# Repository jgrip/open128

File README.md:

## Migrated to codeberg <https://codeberg.org/jgrip/Open128>

View this project on [CADLAB.io](https://cadlab.io/project/24751). 

# open128

This is a clone of the Commodore 128 home computer made with KiCad, licensed under [CC BY-SA 4.0](https://creativecommons.org/licenses/by-sa/4.0/).

It contains both schematic and PCB layout, based on the Neo128 project by me.
This PCB has not yet been manufactured and tested however there are minimal changes compared to the well tested Neo128.

Some of the components have been copied from the [bit-preserve project](https://github.com/baldengineer/bit-preserve) and modified.

For Bill of Material and other documentation, please see https://c128.se

-----
This work is licensed under a
[Creative Commons Attribution-ShareAlike 4.0 International License][cc-by-sa].

[![CC BY-SA 4.0][cc-by-sa-image]][cc-by-sa]

[cc-by-sa]: http://creativecommons.org/licenses/by-sa/4.0/
[cc-by-sa-image]: https://licensebuttons.net/l/by-sa/4.0/88x31.png
[cc-by-sa-shield]: https://img.shields.io/badge/License-CC%20BY--SA%204.0-lightgrey.svg

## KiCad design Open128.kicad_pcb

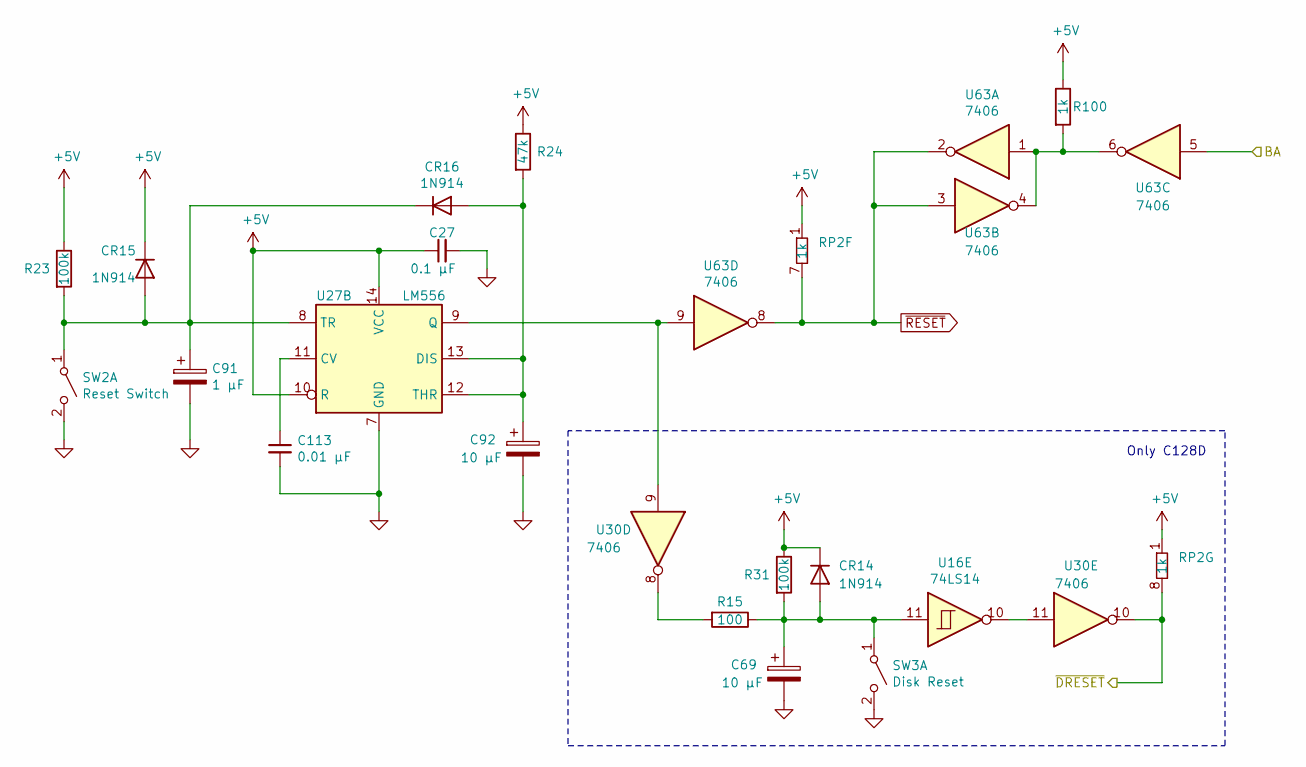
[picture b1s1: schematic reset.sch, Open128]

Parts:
C27: 0.1 µF; C_Disc_D10.0mm_W2.5mm_P5.00mm; Voltage Rating 25V; Voltage Tolerance +80% -20%; Mouser Part 581-SA105E104MAR
C69, C92: 10 µF; CP_Radial_Tantal_D5.0mm_P5.00mm; Voltage Rating 16V; Mouser Part 647-UVR1H100MDD1TD
C91: 1 µF; CP_Radial_Tantal_D5.0mm_P5.00mm; Voltage Rating 16V; Mouser Part 647-USA1H010MDD1TE
C113: 0.01 µF; C_Disc_D10.0mm_W2.5mm_P5.00mm; Voltage Rating 25V; Voltage Tolerance +80% -20%; Mouser Part 581-SA105E103M
CR14, CR15, CR16: 1N914; D_DO-35_SOD27_P12.70mm_Horizontal; Mouser Part 512-1N914
R15: 100; R_Axial_DIN0309_L9.0mm_D2.5mm_P12.70mm_Horizontal; Mouser Part 660-MF1/4DCT52A1000F
R23, R31: 100k; R_Axial_DIN0309_L9.0mm_D2.5mm_P12.70mm_Horizontal; Mouser Part 660-MF1/4LCT52R104J
R24: 47k; R_Axial_DIN0309_L9.0mm_D2.5mm_P12.70mm_Horizontal; Mouser Part 660-MF1/4LCT52R473J
R100: 1k; R_Axial_DIN0309_L9.0mm_D2.5mm_P12.70mm_Horizontal; Mouser Part 660-MF1/4LCT52R102J
RP2: 1k; R_Array_SIP9; Mouser Part 652-4609X-1LF-1K
SW2: Reset Switch; Switch-Pushbutton
SW3: Disk Reset; Switch-Pushbutton
U16: 74LS14; DIP-14_W7.62mm; Mouser Part 595-SN74LS14N
U27: LM556; DIP-14_W7.62mm; Mouser Part 595-NA556N
U30, U63: 7406; DIP-14_W7.62mm; Mouser Part 595-SN74LS06N

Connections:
+5V: C27.1, CR14.1 (K), CR15.1 (K), R23.1, R24.1, R31.1, R100.1, RP2.1 (common), U27.10 (R), U27.14 (VCC); also elsewhere on the board
/BA: U63.5; also elsewhere on the board
/I/O/~DRESET: RP2.8 (R8), U30.10; also elsewhere on the board
GND: C27.2, C69.2, C91.2, C92.2, C113.2, SW2.2 (B), SW3.2 (B), U27.7 (GND); also elsewhere on the board
unnamed: C69.1, CR14.2 (A), R15.1, R31.2, SW3.1 (A), U16.11
unnamed: C91.1, CR15.2 (A), CR16.1 (K), R23.2, SW2.1 (A), U27.8 (TR)
unnamed: C92.1, CR16.2 (A), R24.2, U27.12 (THR), U27.13 (DIS)
unnamed: C113.1, U27.11 (CV)
unnamed: R15.2, U30.8
unnamed: R100.2, U63.1, U63.4, U63.6
unnamed: U16.10, U30.11
unnamed: U27.9 (Q), U30.9, U63.9
~RESET: RP2.7 (R8), U63.2, U63.3, U63.8; also elsewhere on the board

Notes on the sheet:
Only C128D

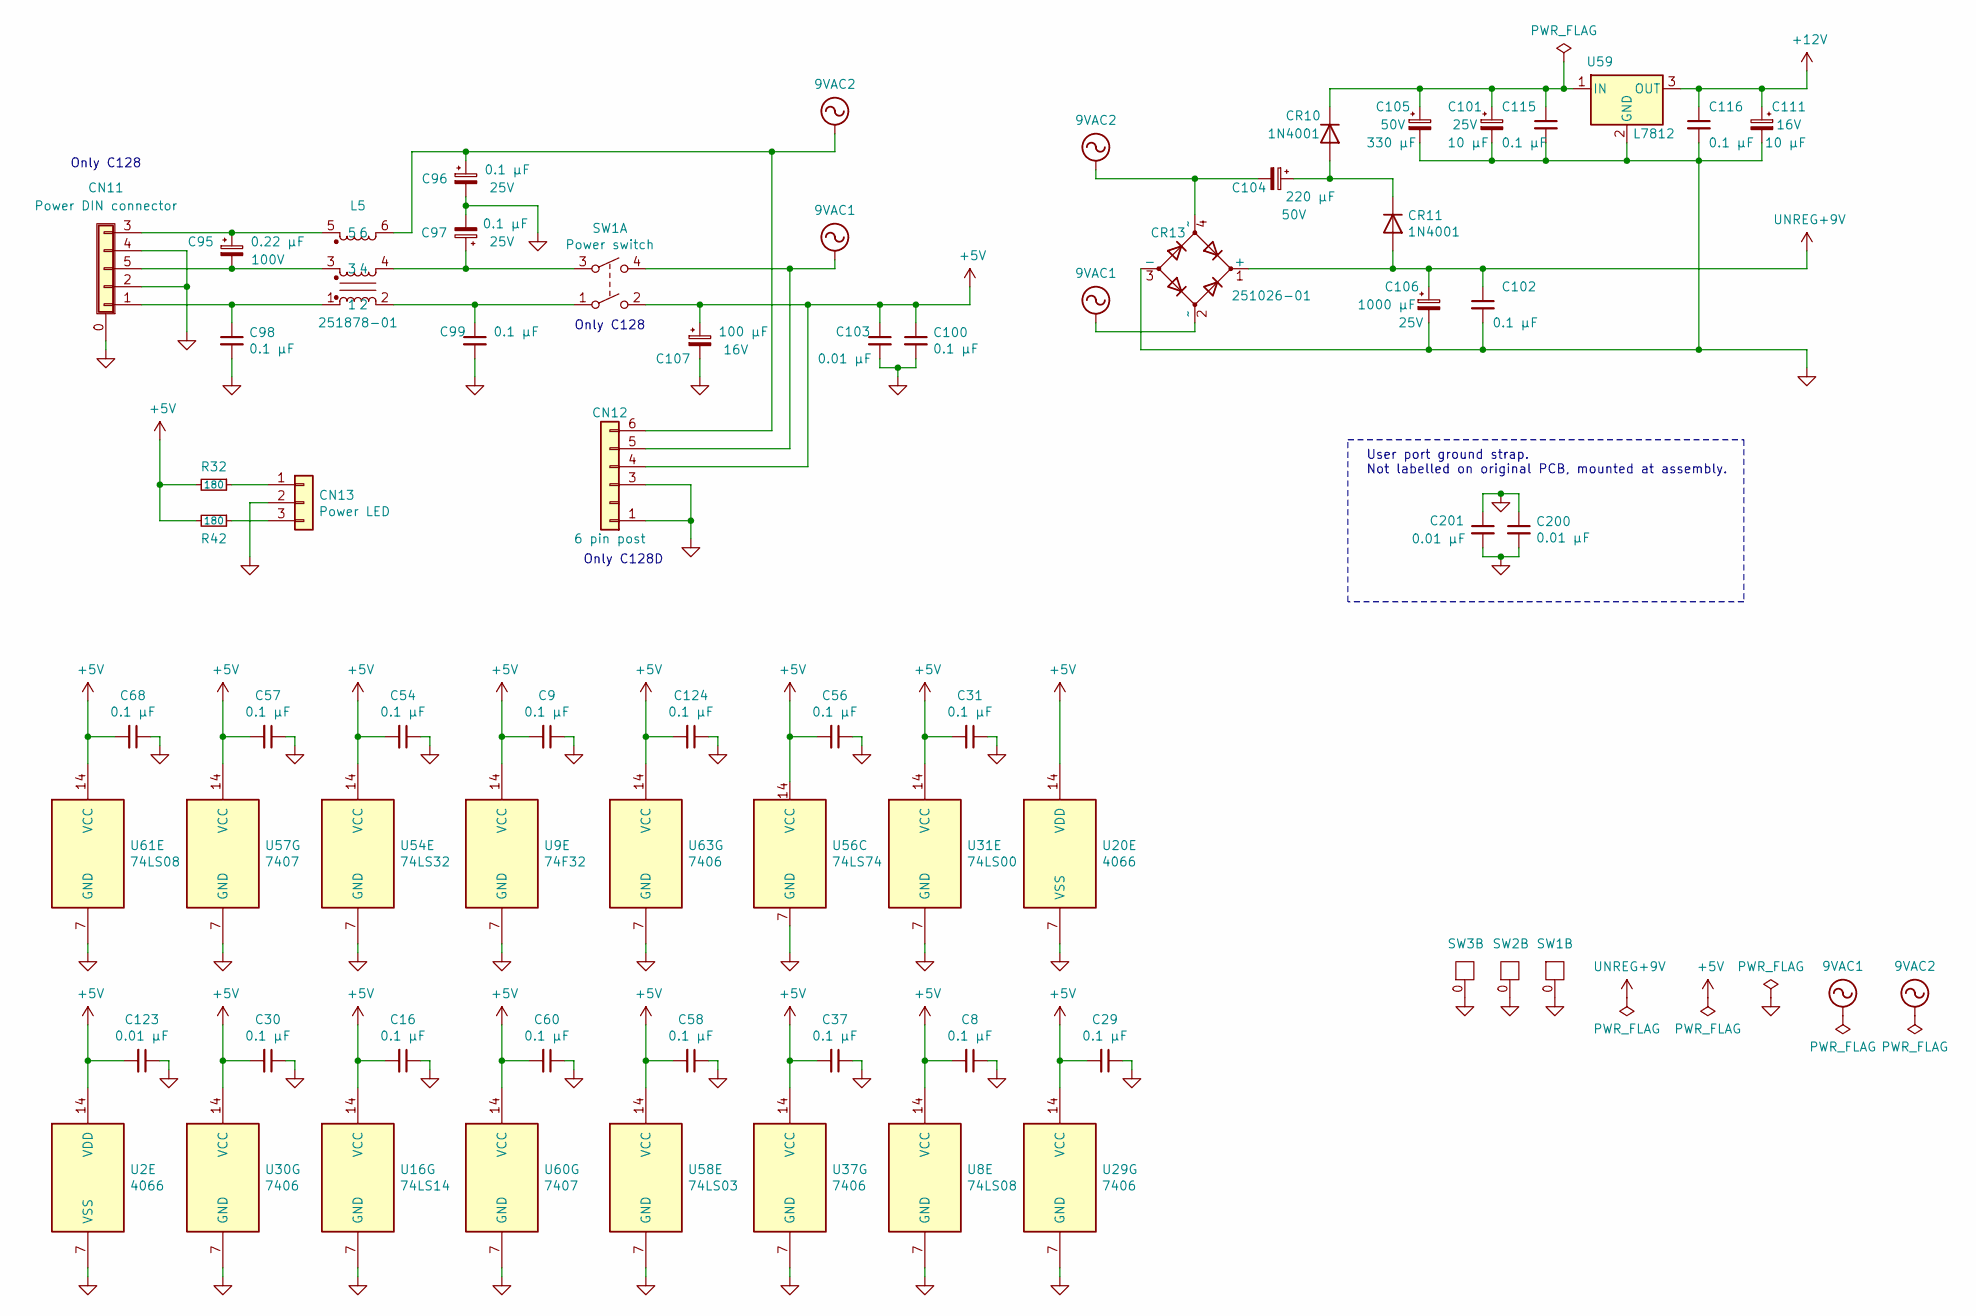
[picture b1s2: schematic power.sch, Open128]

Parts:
C8, C9, C16, C29, C30, C31, C37, C54, C56, C57, C58, C60, C68, C96, C97, C98, C99, C100, C102, C115, C116, C124: 0.1 µF; C_Disc_D10.0mm_W2.5mm_P5.00mm; Voltage Rating 25V; Voltage Tolerance +80% -20%; Mouser Part 581-SA105E104MAR
C95: 0.22 µF; C_Disc_D10.5mm_W5.0mm_P10.00mm; Voltage Rating 100V; Voltage Tolerance +80% -20%; Mouser Part 581-SA115E224MAR
C101: 10 µF; CP_Radial_Tantal_D5.0mm_P5.00mm; Voltage Rating 25V; Voltage Tolerance +80% -20%; Mouser Part 647-UVR1H100MDD1TD
C103, C123, C200, C201: 0.01 µF; C_Disc_D10.0mm_W2.5mm_P5.00mm; Voltage Rating 25V; Voltage Tolerance +80% -20%; Mouser Part 581-SA105E103M
C104: 220 µF; CP_Radial_Tantal_D8.0mm_P5.00mm; Voltage Rating 50V; Voltage Tolerance +80% -20%; Mouser Part 647-UVZ1H221MPD1TD
C105: 330 µF; CP_Radial_Tantal_D8.0mm_P5.00mm; Voltage Rating 50V; Voltage Tolerance +80% -20%; Mouser Part 647-UVZ1H331MPD1TD
C106: 1000 µF; CP_Axial_L34.5mm_D20.0mm_P41.00mm_Horizontal; Voltage Rating 25V; Voltage Tolerance +80% -20%; Mouser Part 647-TVX1H102MCD
C107: 100 µF; CP_Radial_Tantal_D10.5mm_P5.00mm; Voltage Rating 16V; Voltage Tolerance +80% -20%; Mouser Part 647-UVR1C101MDD1TD
C111: 10 µF; CP_Radial_Tantal_D5.0mm_P5.00mm; Voltage Rating 16V; Voltage Tolerance +80% -20%; Mouser Part 647-UVR1H100MDD1TD
CN11: Power DIN connector; Connector_Power_5pin_252167_01
CN12: 6 pin post; CN12_C128D_power
CN13: Power LED; PinHeader_1x03_P2.54mm_Vertical; Mouser Part 538-22-03-2031
CR10, CR11: 1N4001; D_DO-41_SOD81_P12.70mm_Horizontal; Mouser Part 625-1N4001-E3/54
CR13: 251026-01; BRIDGE_RECTIFIER
L5: 251878-01; Noise_Filter_Power_251878_01
R32, R42: 180; R_Axial_DIN0309_L9.0mm_D2.5mm_P12.70mm_Horizontal; Mouser Part 660-MF1/4DCT52R1800F
SW1: Power switch; Power_Switch
SW2: Reset Switch; Switch-Pushbutton
SW3: Disk Reset; Switch-Pushbutton
U2, U20: 4066; DIP-14_W7.62mm; Mouser Part 595-CD74HCT4066E
U8, U61: 74LS08; DIP-14_W7.62mm; Mouser Part 595-SN74LS08N
U9: 74F32; DIP-14_W7.62mm; Mouser Part 595-SN74F32N
U16: 74LS14; DIP-14_W7.62mm; Mouser Part 595-SN74LS14N
U29, U30, U37, U63: 7406; DIP-14_W7.62mm; Mouser Part 595-SN74LS06N
U31: 74LS00; DIP-14_W7.62mm; Mouser Part 595-SN74LS00N
U54: 74LS32; DIP-14_W7.62mm; Mouser Part 595-SN74LS32N
U56: 74LS74; DIP-14_W7.62mm; Mouser Part 595-SN74LS74AN
U57, U60: 7407; DIP-14_W7.62mm; Mouser Part 595-SN74LS07N
U58: 74LS03; DIP-14_W7.62mm; Mouser Part 595-SN74LS03N
U59: L7812; TO-220-3_Horizontal_TabDown; Mouser Part 511-L7812CV

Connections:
9VAC1: CN12.5, CR13.2 (~~), SW1.4; also elsewhere on the board
9VAC2: C96.1, C104.2, CN12.6, CR13.4 (~~), L5.6; also elsewhere on the board
+5V: C8.2, C9.2, C16.2, C29.2, C30.2, C31.2, C37.2, C54.2, C56.2, C57.2, C58.2, C60.2, C68.2, C100.1, C103.1, C107.1, C123.2, C124.2, CN12.4, R32.2, R42.2, SW1.2, U2.14 (VDD), U8.14 (VCC), U9.14 (VCC), U16.14 (VCC), U20.14 (VDD), U29.14 (VCC), U30.14 (VCC), U31.14 (VCC), U37.14 (VCC), U54.14 (VCC), U56.14 (VCC), U57.14 (VCC), U58.14 (VCC), U60.14 (VCC), U61.14 (VCC), U63.14 (VCC); also elsewhere on the board
+9V: C102.1, C106.1, CR11.2 (A), CR13.1 (+); also elsewhere on the board
+12V: C111.1, C116.1, U59.3 (OUT); also elsewhere on the board
GND: C8.1, C9.1, C16.1, C29.1, C30.1, C31.1, C37.1, C54.1, C56.1, C57.1, C58.1, C60.1, C68.1, C96.2, C97.2, C98.2, C99.2, C100.2, C101.2, C102.2, C103.2, C105.2, C106.2, C107.2, C111.2, C115.2, C116.2, C123.1, C124.1, C200.1, C200.2, C201.1, C201.2, CN11.0 (Shield), CN11.2, CN11.4, CN12.1, CN12.3, CN13.2, CR13.3 (-), SW1.0 (GND), SW2.0 (GND), SW3.0 (GND), U2.7 (VSS), U8.7 (GND), U9.7 (GND), U16.7 (GND), U20.7 (VSS), U29.7 (GND), U30.7 (GND), U31.7 (GND), U37.7 (GND), U54.7 (GND), U56.7 (GND), U57.7 (GND), U58.7 (GND), U59.2 (GND), U60.7 (GND), U61.7 (GND), U63.7 (GND); also elsewhere on the board
unnamed: C95.1, CN11.3, L5.5
unnamed: C95.2, CN11.5, L5.3
unnamed: C97.1, L5.4, SW1.3
unnamed: C98.1, CN11.1, L5.1
unnamed: C99.1, L5.2, SW1.1
unnamed: C101.1, C105.1, C115.1, CR10.1 (K), U59.1 (IN)
unnamed: C104.1, CR10.2 (A), CR11.1 (K)
unnamed: CN13.1, R32.1
unnamed: CN13.3, R42.1

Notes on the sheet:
Only C128
Only C128D
User port ground strap. Not labelled on original PCB, mounted at assembly.

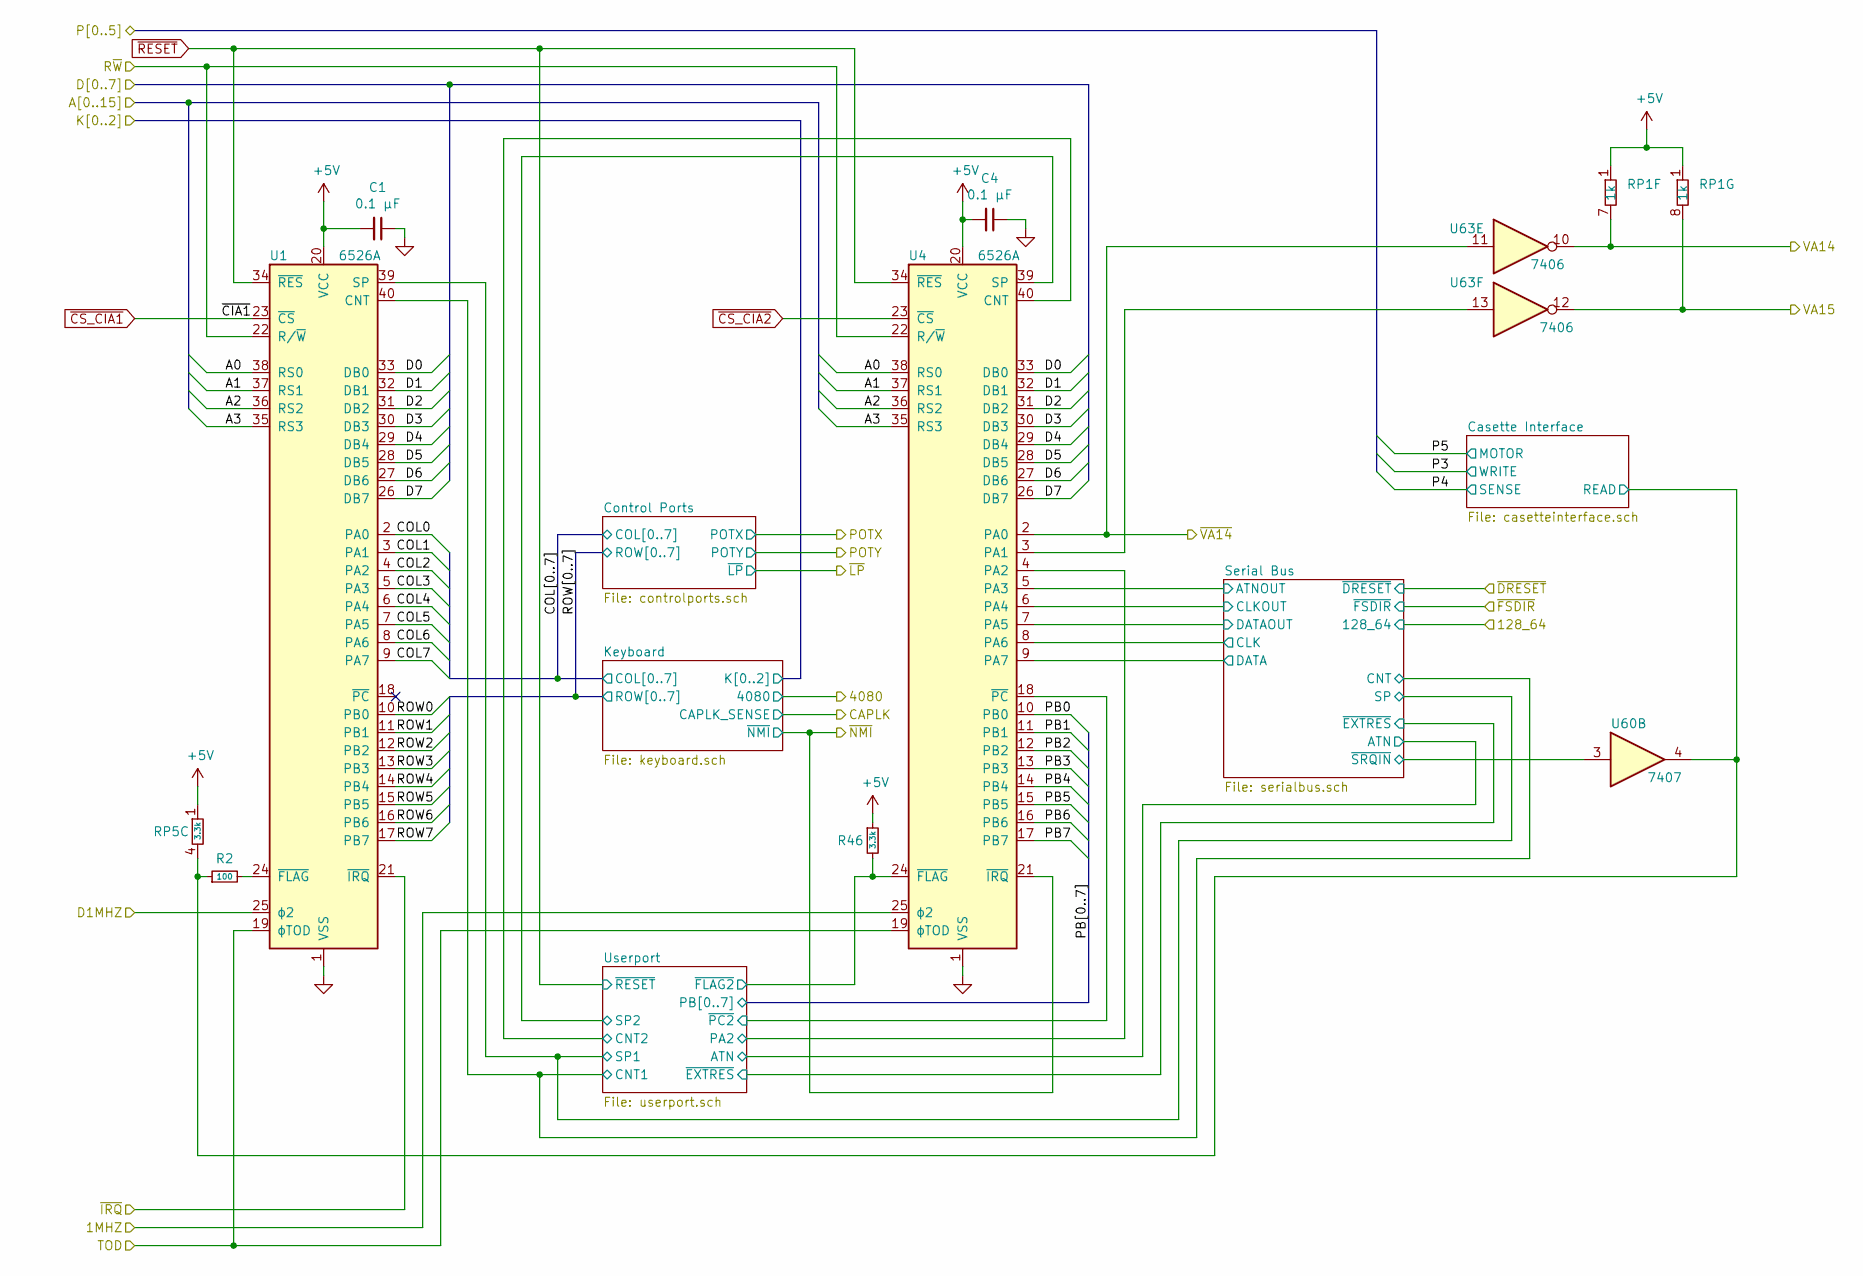
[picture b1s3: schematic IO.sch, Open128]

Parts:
C1, C4: 0.1 µF; C_Disc_D10.0mm_W2.5mm_P5.00mm; Voltage Rating 25V; Voltage Tolerance +80% -20%; Mouser Part 581-SA105E104MAR
R2: 100; R_Axial_DIN0309_L9.0mm_D2.5mm_P12.70mm_Horizontal; Mouser Part 660-MF1/4DCT52A1000F
R46: 3.3k; R_Axial_DIN0309_L9.0mm_D2.5mm_P12.70mm_Horizontal; Mouser Part 660-MF1/4LCT52R332J
RP1: 1k; R_Array_SIP8; Mouser Part 652-4608X-1LF-1K
RP5: 3.3k; R_Array_SIP8; Mouser Part 652-4608X-1LF-3.3K
U1, U4: 6526A; DIP-40_W15.24mm_Socket
U60: 7407; DIP-14_W7.62mm; Mouser Part 595-SN74LS07N
U63: 7406; DIP-14_W7.62mm; Mouser Part 595-SN74LS06N

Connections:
+5V: C1.2, C4.2, R46.1, RP1.1 (common), RP5.1 (common), U1.20 (VCC), U4.20 (VCC); also elsewhere on the board
/Address Multiplexing/A0: U1.38 (RS0), U4.38 (RS0); also elsewhere on the board
/Address Multiplexing/A1: U1.37 (RS1), U4.37 (RS1); also elsewhere on the board
/Address Multiplexing/A2: U1.36 (RS2), U4.36 (RS2); also elsewhere on the board
/Address Multiplexing/A3: U1.35 (RS3), U4.35 (RS3); also elsewhere on the board
/Address Multiplexing/VA14: RP1.7 (R6), U63.10; also elsewhere on the board
/Address Multiplexing/VA15: RP1.8 (R7), U63.12; also elsewhere on the board
/CPU 8502/D0: U1.33 (DB0), U4.33 (DB0); also elsewhere on the board
/CPU 8502/D1: U1.32 (DB1), U4.32 (DB1); also elsewhere on the board
/CPU 8502/D2: U1.31 (DB2), U4.31 (DB2); also elsewhere on the board
/CPU 8502/D3: U1.30 (DB3), U4.30 (DB3); also elsewhere on the board
/CPU 8502/D4: U1.29 (DB4), U4.29 (DB4); also elsewhere on the board
/CPU 8502/D5: U1.28 (DB5), U4.28 (DB5); also elsewhere on the board
/CPU 8502/D6: U1.27 (DB6), U4.27 (DB6); also elsewhere on the board
/CPU 8502/D7: U1.26 (DB7), U4.26 (DB7); also elsewhere on the board
/CPU 8502/~NMI: U4.21 (~IRQ); also elsewhere on the board
/CPU Z80/D1MHZ: U1.25 (ϕ2); also elsewhere on the board
/Clock/TOD: U1.19 (ϕTOD), U4.19 (ϕTOD); also elsewhere on the board
/Expansion Port/1MHZ: U4.25 (ϕ2); also elsewhere on the board
/I/O/COL0: U1.2 (PA0); also elsewhere on the board
/I/O/COL1: U1.3 (PA1); also elsewhere on the board
/I/O/COL2: U1.4 (PA2); also elsewhere on the board
/I/O/COL3: U1.5 (PA3); also elsewhere on the board
/I/O/COL4: U1.6 (PA4); also elsewhere on the board
/I/O/COL5: U1.7 (PA5); also elsewhere on the board
/I/O/COL6: U1.8 (PA6); also elsewhere on the board
/I/O/COL7: U1.9 (PA7); also elsewhere on the board
/I/O/Casette Interface/READ: R2.1, RP5.4 (R3), U60.4; also elsewhere on the board
/I/O/PB0: U4.10 (PB0); also elsewhere on the board
/I/O/PB1: U4.11 (PB1); also elsewhere on the board
/I/O/PB2: U4.12 (PB2); also elsewhere on the board
/I/O/PB3: U4.13 (PB3); also elsewhere on the board
/I/O/PB4: U4.14 (PB4); also elsewhere on the board
/I/O/PB5: U4.15 (PB5); also elsewhere on the board
/I/O/PB6: U4.16 (PB6); also elsewhere on the board
/I/O/PB7: U4.17 (PB7); also elsewhere on the board
/I/O/ROW0: U1.10 (PB0); also elsewhere on the board
/I/O/ROW1: U1.11 (PB1); also elsewhere on the board
/I/O/ROW2: U1.12 (PB2); also elsewhere on the board
/I/O/ROW3: U1.13 (PB3); also elsewhere on the board
/I/O/ROW5: U1.15 (PB5); also elsewhere on the board
/I/O/ROW6: U1.16 (PB6); also elsewhere on the board
/I/O/ROW7: U1.17 (PB7); also elsewhere on the board
/I/O/Serial Bus/ATNOUT: U4.5 (PA3); also elsewhere on the board
/I/O/Serial Bus/CLK: U4.8 (PA6); also elsewhere on the board
/I/O/Serial Bus/CLKOUT: U4.6 (PA4); also elsewhere on the board
/I/O/Serial Bus/CNT: U1.40 (CNT); also elsewhere on the board
/I/O/Serial Bus/DATA: U4.9 (PA7); also elsewhere on the board
/I/O/Serial Bus/DATAOUT: U4.7 (PA5); also elsewhere on the board
/I/O/Serial Bus/SP: U1.39 (SP); also elsewhere on the board
/I/O/Serial Bus/~SRQIN: U60.3; also elsewhere on the board
/I/O/Userport/CNT2: U4.40 (CNT); also elsewhere on the board
/I/O/Userport/PA2: U4.4 (PA2); also elsewhere on the board
/I/O/Userport/SP2: U4.39 (SP); also elsewhere on the board
/I/O/Userport/~FLAG2: R46.2, U4.24 (~FLAG); also elsewhere on the board
/I/O/Userport/~PC2: U4.18 (~PC); also elsewhere on the board
/I/O/~VA14: U4.2 (PA0), U63.11; also elsewhere on the board
/R~W: U1.22 (R/~W), U4.22 (R/~W); also elsewhere on the board
/VIC/~LIGHTPEN: U1.14 (PB4); also elsewhere on the board
/~IRQ: U1.21 (~IRQ); also elsewhere on the board
GND: C1.1, C4.1, U1.1 (VSS), U4.1 (VSS); also elsewhere on the board
unnamed: R2.2, U1.24 (~FLAG)
unnamed: U4.3 (PA1), U63.13
~CS_CIA1: U1.23 (~CS); also elsewhere on the board
~CS_CIA2: U4.23 (~CS); also elsewhere on the board
~RESET: U1.34 (~RES), U4.34 (~RES); also elsewhere on the board

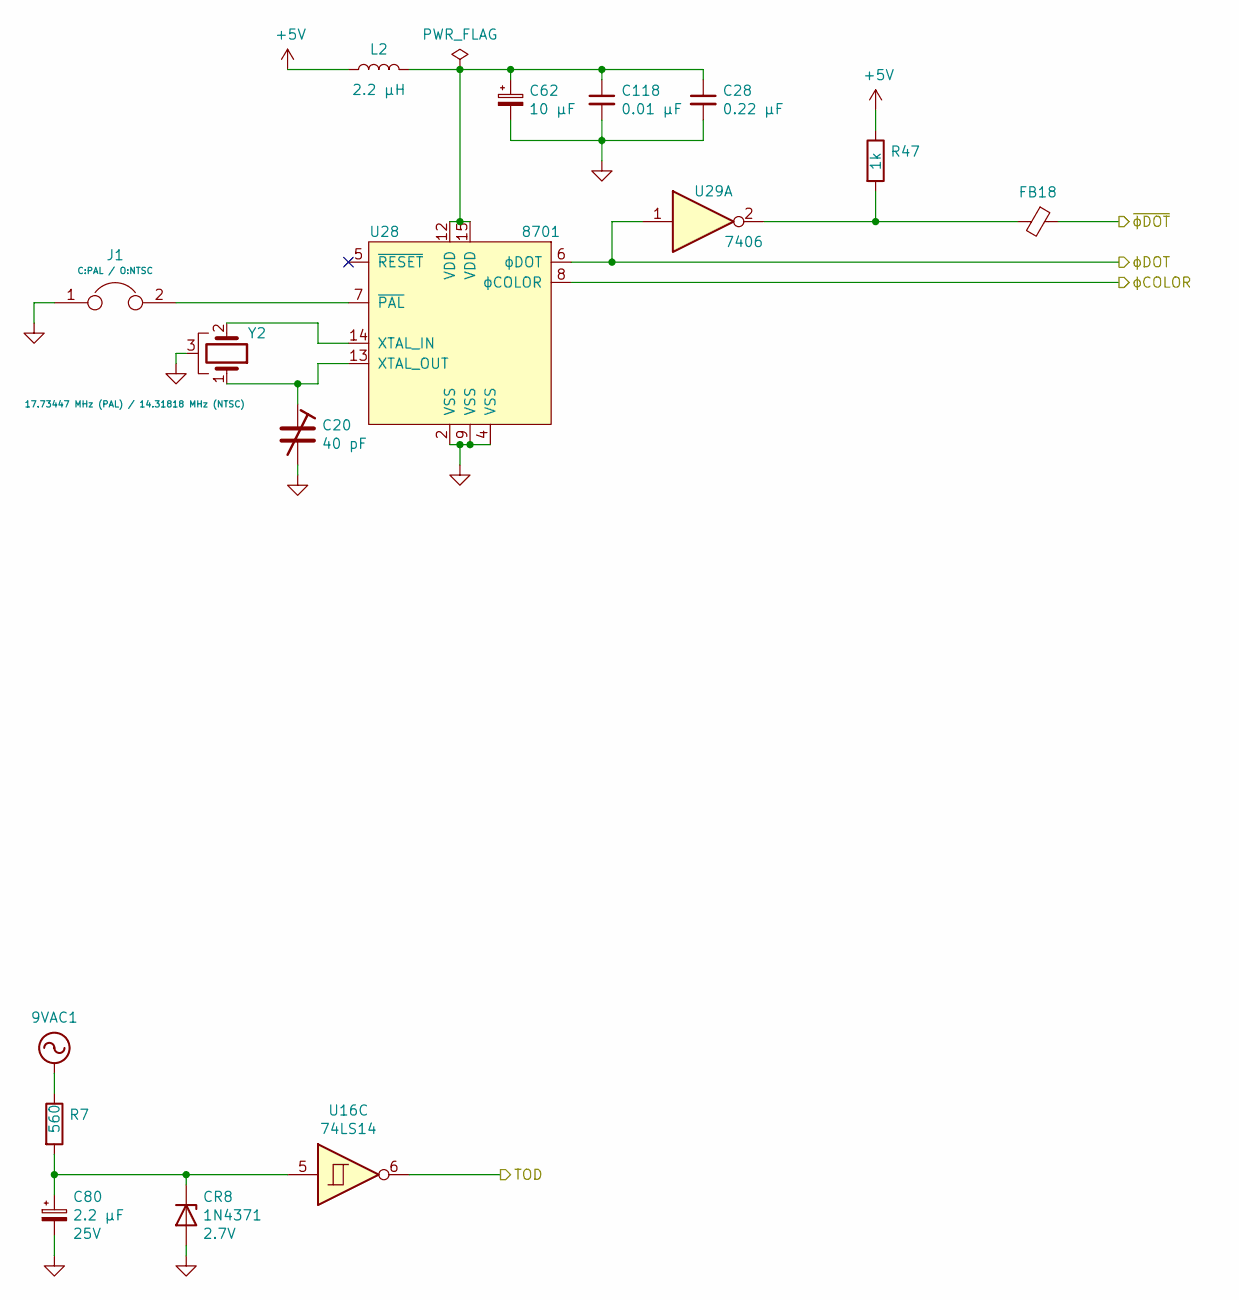
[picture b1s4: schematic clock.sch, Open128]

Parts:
C20: 40 pF; C_Adjustable_L7.0mm_W4.5mm_P5.00mm
C28: 0.22 µF; C_Disc_D10.0mm_W2.5mm_P5.00mm; Mouser Part 581-SA115E224MAR
C62: 10 µF; CP_Radial_Tantal_D5.0mm_P5.00mm; Voltage Rating 16V; Mouser Part 647-UVR1H100MDD1TD
C80: 2.2 µF; CP_Radial_Tantal_D5.0mm_P5.00mm; Voltage Rating 25V; Mouser Part 647-UVR1H2R2MDD1TD
C118: 0.01 µF; C_Disc_D10.0mm_W2.5mm_P5.00mm; Voltage Rating 25V; Voltage Tolerance +80% -20%; Mouser Part 581-SA105E103M
CR8: 1N4371; D_DO-35_SOD27_P12.70mm_Horizontal; Zener Voltage 2.7V; Mouser Part 512-BZX79C2V7
FB18: Ferrite_Bead_Small; Ferrite_Bead_vertical; Mouser Part 81-BL02RN2R1M2B
J1: C:PAL / O:NTSC; PinHeader_1x02_P2.54mm_Vertical
L2: 2.2 µH; L_Axial_L9.5mm_D4.0mm_P12.70mm_Horizontal_Fastron_SMCC; Mouser Part 871-B78108S1222K
R7: 560; R_Axial_DIN0309_L9.0mm_D2.5mm_P12.70mm_Horizontal; Mouser Part 660-MF1/4DCT52R5600F
R47: 1k; R_Axial_DIN0309_L9.0mm_D2.5mm_P12.70mm_Horizontal; Mouser Part 660-MF1/4DCT52R5600F
U16: 74LS14; DIP-14_W7.62mm; Mouser Part 595-SN74LS14N
U28: 8701; DIP-16_W7.62mm_Socket
U29: 7406; DIP-14_W7.62mm; Mouser Part 595-SN74LS06N
Y2: 17.73447 MHz (PAL) / 14.31818 MHz (NTSC); Crystal_HC49-U_Horizontal_1EP_style2

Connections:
9VAC1: R7.1; also elsewhere on the board
+5V: L2.1, R47.1; also elsewhere on the board
/Clock/TOD: U16.6; also elsewhere on the board
/Clock/~ϕDOT: FB18.1; also elsewhere on the board
/VIC/ΦCOLOR: U28.8 (ϕCOLOR); also elsewhere on the board
/VIC/ΦDOT: U28.6 (ϕDOT), U29.1; also elsewhere on the board
GND: C20.2, C28.2, C62.2, C80.2, C118.2, CR8.2 (A), FB18.3 (GND), J1.1, U28.2 (VSS), U28.4 (VSS), U28.9 (VSS), Y2.3; also elsewhere on the board
unnamed: C20.1, U28.13 (XTAL_OUT), Y2.1
unnamed: C80.1, CR8.1 (K), R7.2, U16.5
unnamed: C28.1, C62.1, C118.1, L2.2, U28.12 (VDD), U28.15 (VDD)
unnamed: FB18.2, R47.2, U29.2
unnamed: J1.2, U28.7 (~PAL)
unnamed: U28.14 (XTAL_IN), Y2.2

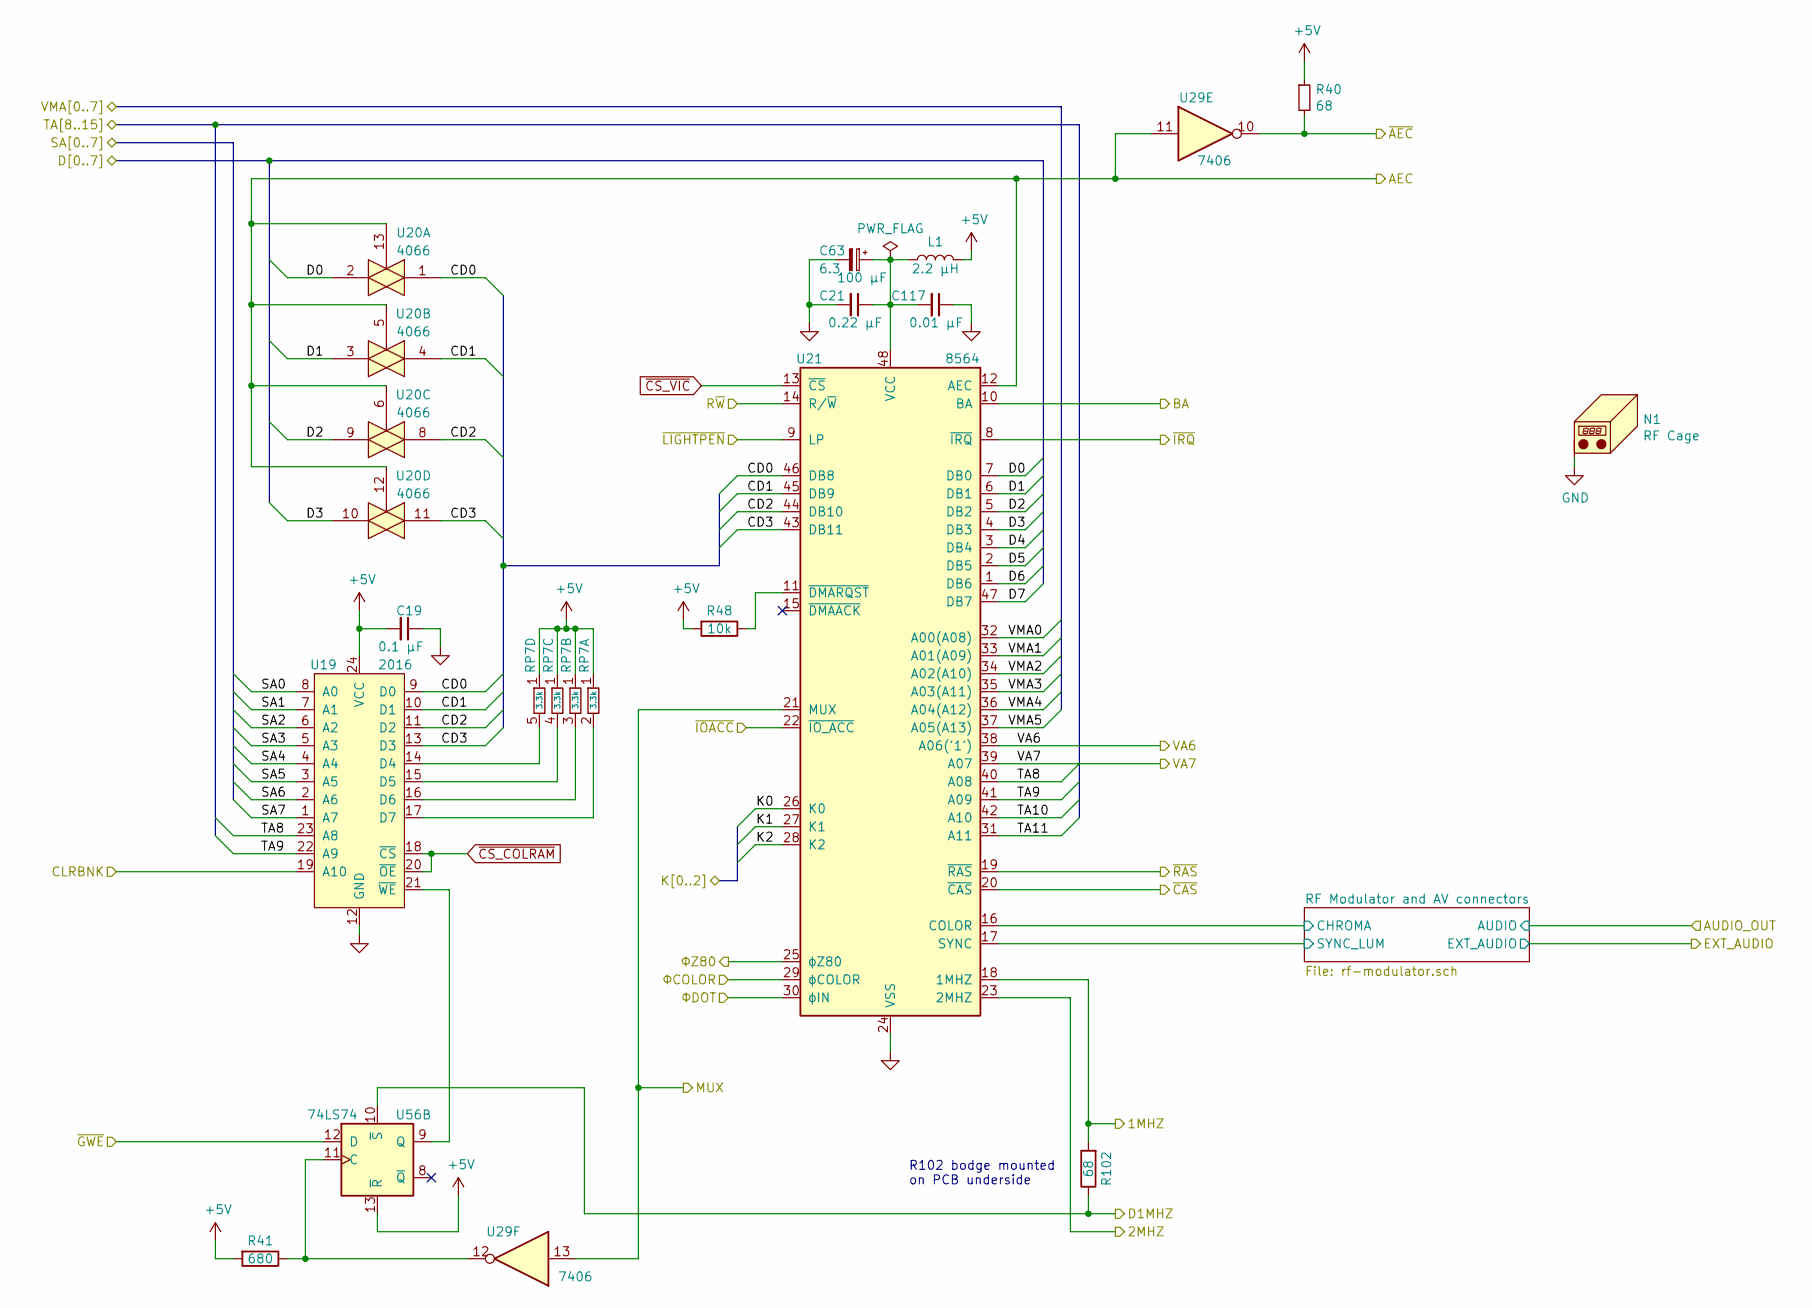
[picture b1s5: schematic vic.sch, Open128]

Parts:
C19: 0.1 µF; C_Disc_D10.0mm_W2.5mm_P5.00mm; Voltage Rating 25V; Voltage Tolerance +80% -20%; Mouser Part 581-SA105E104MAR
C21: 0.22 µF; C_Disc_D7.5mm_W2.5mm_P5.00mm; Mouser Part 581-SA115E224MAR
C63: 100 µF; CP_Radial_Tantal_D5.0mm_P5.00mm; Voltage Rating 6.3; Voltage Tolerance +80% / -20%; Mouser Part 647-UVR1H100MDD1TD
C117: 0.01 µF; C_Disc_D10.0mm_W2.5mm_P5.00mm; Voltage Rating 25V; Voltage Tolerance +80% -20%; Mouser Part 581-SA105E103M
L1: 2.2 µH; L_Axial_L9.5mm_D4.0mm_P12.70mm_Horizontal_Fastron_SMCC; Mouser Part 871-B78108S1222K
N1: RF Cage; RF_Cage
R40, R102: 68; R_Axial_DIN0309_L9.0mm_D2.5mm_P12.70mm_Horizontal; Mouser Part 660-MF1/4DCT52R68R0F
R41: 680; R_Axial_DIN0309_L9.0mm_D2.5mm_P12.70mm_Horizontal; Mouser Part 660-MF1/4LCT52R681J
R48: 10k; R_Axial_DIN0309_L9.0mm_D2.5mm_P12.70mm_Horizontal; Mouser Part 660-MF1/4LCT52R103J
RP7: 3.3k; R_Array_SIP10; Mouser Part 652-4610X-1LF-3.3K
U19: 2016; DIP-24_W15.24mm_Socket
U20: 4066; DIP-14_W7.62mm; Mouser Part 595-CD74HCT4066E
U21: 8564; DIP-48_W15.24mm_Socket
U29: 7406; DIP-14_W7.62mm; Mouser Part 595-SN74LS06N
U56: 74LS74; DIP-14_W7.62mm; Mouser Part 595-SN74LS74AN

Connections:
+5V: C19.2, L1.2, R40.1, R41.2, R48.2, RP7.1 (common), U19.24 (VCC), U56.13 (~R); also elsewhere on the board
/AEC: U20.5, U20.6, U20.12, U20.13, U21.12 (AEC), U29.11; also elsewhere on the board
/Address Multiplexing/MUX: U21.21 (MUX), U29.13; also elsewhere on the board
/Address Multiplexing/SA0: U19.8 (A0); also elsewhere on the board
/Address Multiplexing/SA1: U19.7 (A1); also elsewhere on the board
/Address Multiplexing/SA2: U19.6 (A2); also elsewhere on the board
/Address Multiplexing/SA3: U19.5 (A3); also elsewhere on the board
/Address Multiplexing/SA4: U19.4 (A4); also elsewhere on the board
/Address Multiplexing/SA5: U19.3 (A5); also elsewhere on the board
/Address Multiplexing/SA6: U19.2 (A6); also elsewhere on the board
/Address Multiplexing/SA7: U19.1 (A7); also elsewhere on the board
/Address Multiplexing/TA8: U19.23 (A8), U21.40 (A08); also elsewhere on the board
/Address Multiplexing/TA9: U19.22 (A9), U21.41 (A09); also elsewhere on the board
/Address Multiplexing/TA10: U21.42 (A10); also elsewhere on the board
/Address Multiplexing/TA11: U21.31 (A11); also elsewhere on the board
/Address Multiplexing/VA6: U21.38 (A06('1')); also elsewhere on the board
/Address Multiplexing/VA7: U21.39 (A07); also elsewhere on the board
/Address Multiplexing/VMA0: U21.32 (A00(A08)); also elsewhere on the board
/Address Multiplexing/VMA1: U21.33 (A01(A09)); also elsewhere on the board
/Address Multiplexing/VMA2: U21.34 (A02(A10)); also elsewhere on the board
/Address Multiplexing/VMA3: U21.35 (A03(A11)); also elsewhere on the board
/Address Multiplexing/VMA4: U21.36 (A04(A12)); also elsewhere on the board
/Address Multiplexing/VMA5: U21.37 (A05(A13)); also elsewhere on the board
/Address Multiplexing/~AEC: R40.2, U29.10; also elsewhere on the board
/Address Multiplexing/~RAS: U21.19 (~RAS); also elsewhere on the board
/BA: U21.10 (BA); also elsewhere on the board
/CPU 8502/2MHZ: U21.23 (2MHZ); also elsewhere on the board
/CPU 8502/D0: U20.2, U21.7 (DB0); also elsewhere on the board
/CPU 8502/D1: U20.3, U21.6 (DB1); also elsewhere on the board
/CPU 8502/D2: U20.9, U21.5 (DB2); also elsewhere on the board
/CPU 8502/D3: U20.10, U21.4 (DB3); also elsewhere on the board
/CPU 8502/D4: U21.3 (DB4); also elsewhere on the board
/CPU 8502/D5: U21.2 (DB5); also elsewhere on the board
/CPU 8502/D6: U21.1 (DB6); also elsewhere on the board
/CPU 8502/D7: U21.47 (DB7); also elsewhere on the board
/CPU Z80/D1MHZ: R102.1, U56.10 (~S); also elsewhere on the board
/CPU Z80/ΦZ80: U21.25 (ϕZ80); also elsewhere on the board
/DRAM/~CAS: U21.20 (~CAS); also elsewhere on the board
/Expansion Port/1MHZ: R102.2, U21.18 (1MHZ); also elsewhere on the board
/Memory Management/CLRBNK: U19.19 (A10); also elsewhere on the board
/Memory Management/~GWE: U56.12 (D); also elsewhere on the board
/Memory Management/~IOACC: U21.22 (~IO_ACC); also elsewhere on the board
/R~W: U21.14 (R/~W); also elsewhere on the board
/VIC/CD0: U19.9 (D0), U20.1, U21.46 (DB8)
/VIC/CD1: U19.10 (D1), U20.4, U21.45 (DB9)
/VIC/CD2: U19.11 (D2), U20.8, U21.44 (DB10)
/VIC/CD3: U19.13 (D3), U20.11, U21.43 (DB11)
/VIC/K0: U21.26 (K0); also elsewhere on the board
/VIC/K1: U21.27 (K1); also elsewhere on the board
/VIC/K2: U21.28 (K2); also elsewhere on the board
/VIC/RF Modulator and AV connectors/CHROMA: U21.16 (COLOR); also elsewhere on the board
/VIC/RF Modulator and AV connectors/SYNC_LUM: U21.17 (SYNC); also elsewhere on the board
/VIC/~LIGHTPEN: U21.9 (LP); also elsewhere on the board
/VIC/ΦCOLOR: U21.29 (ϕCOLOR); also elsewhere on the board
/VIC/ΦDOT: U21.30 (ϕIN); also elsewhere on the board
/~IRQ: U21.8 (~IRQ); also elsewhere on the board
GND: C19.1, C21.2, C63.2, C117.1, N1.1, U19.12 (GND), U21.24 (VSS); also elsewhere on the board
unnamed: C21.1, C63.1, C117.2, L1.1, U21.48 (VCC)
unnamed: R41.1, U29.12, U56.11 (C)
unnamed: R48.1, U21.11 (~DMARQST)
unnamed: RP7.2 (R1), U19.17 (D7)
unnamed: RP7.3 (R2), U19.16 (D6)
unnamed: RP7.4 (R3), U19.15 (D5)
unnamed: RP7.5 (R4), U19.14 (D4)
unnamed: U19.21 (~WE), U56.9 (Q)
~CS_COLRAM: U19.18 (~CS), U19.20 (~OE); also elsewhere on the board
~CS_VIC: U21.13 (~CS); also elsewhere on the board

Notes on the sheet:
R102 bodge mounted on PCB underside
